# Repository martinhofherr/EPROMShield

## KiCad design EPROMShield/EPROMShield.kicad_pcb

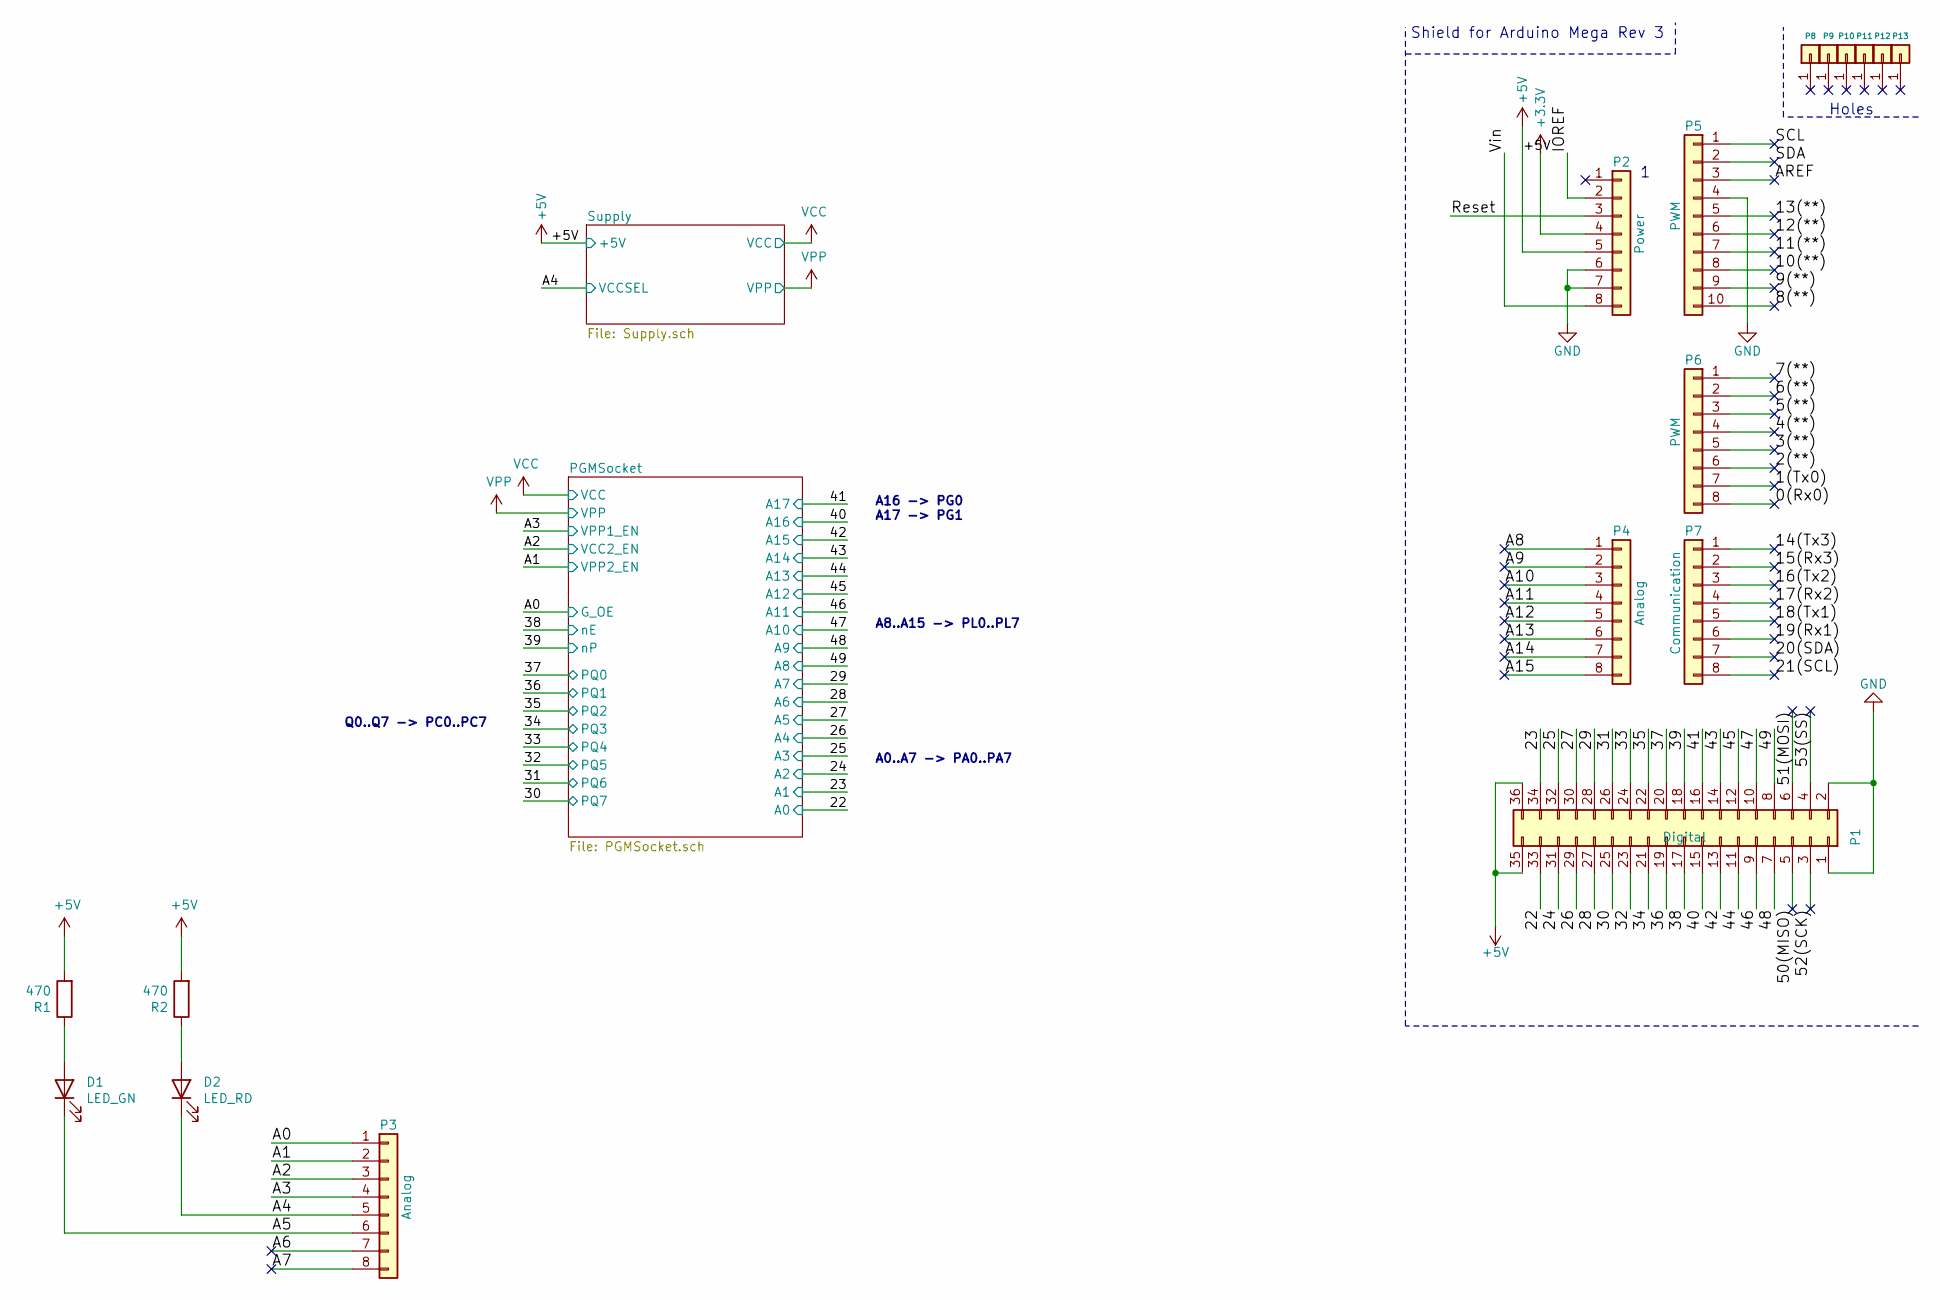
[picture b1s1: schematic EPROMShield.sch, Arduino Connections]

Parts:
D1: LED_GN; LED_1206_3216Metric_Pad1.42x1.75mm_HandSolder
D2: LED_RD; LED_1206_3216Metric_Pad1.42x1.75mm_HandSolder
P1: Digital; Socket_Strip_Arduino_2x18
P2: Power; Socket_Strip_Arduino_1x08
P3, P4: Analog; Socket_Strip_Arduino_1x08
P5: PWM; Socket_Strip_Arduino_1x10
P6: PWM; Socket_Strip_Arduino_1x08
P7: Communication; Socket_Strip_Arduino_1x08
P8, P9, P10, P11, P12, P13: CONN_01X01; Arduino_1pin
R1, R2: 470; R_0805_2012Metric_Pad1.20x1.40mm_HandSolder

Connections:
+3V3: P2.4
+5V: P1.35, P1.36, P2.5, R1.2, R2.2; also elsewhere on the board
/0(Rx0): P6.8
/1(Tx0): P6.7
/2(**): P6.6
/3(**): P6.5
/4(**): P6.4
/5(**): P6.3
/6(**): P6.2
/7(**): P6.1
/8(**): P5.10
/9(**): P5.9
/10(**): P5.8
/11(**): P5.7
/12(**): P5.6
/13(**): P5.5
/14(Tx3): P7.1
/15(Rx3): P7.2
/16(Tx2): P7.3
/17(Rx2): P7.4
/18(Tx1): P7.5
/19(Rx1): P7.6
/20(SDA): P7.7
/21(SCL): P7.8
/22: P1.33; also elsewhere on the board
/23: P1.34; also elsewhere on the board
/24: P1.31; also elsewhere on the board
/25: P1.32; also elsewhere on the board
/26: P1.29; also elsewhere on the board
/27: P1.30; also elsewhere on the board
/28: P1.27; also elsewhere on the board
/29: P1.28; also elsewhere on the board
/30: P1.25; also elsewhere on the board
/31: P1.26; also elsewhere on the board
/32: P1.23; also elsewhere on the board
/33: P1.24; also elsewhere on the board
/34: P1.21; also elsewhere on the board
/35: P1.22; also elsewhere on the board
/36: P1.19; also elsewhere on the board
/37: P1.20; also elsewhere on the board
/38: P1.17; also elsewhere on the board
/39: P1.18; also elsewhere on the board
/40: P1.15; also elsewhere on the board
/41: P1.16; also elsewhere on the board
/42: P1.13; also elsewhere on the board
/43: P1.14; also elsewhere on the board
/44: P1.11; also elsewhere on the board
/45: P1.12; also elsewhere on the board
/46: P1.9; also elsewhere on the board
/47: P1.10; also elsewhere on the board
/48: P1.7; also elsewhere on the board
/49: P1.8; also elsewhere on the board
/50(MISO): P1.5
/51(MOSI): P1.6
/52(SCK): P1.3
/53(SS): P1.4
/A0: P3.1; also elsewhere on the board
/A1: P3.2; also elsewhere on the board
/A2: P3.3; also elsewhere on the board
/A3: P3.4; also elsewhere on the board
/A4: D2.1 (K), P3.5; also elsewhere on the board
/A5: D1.1 (K), P3.6
/A6: P3.7
/A7: P3.8
/A8: P4.1
/A9: P4.2
/A10: P4.3
/A11: P4.4
/A12: P4.5
/A13: P4.6
/A14: P4.7
/A15: P4.8
/AREF: P5.3
/IOREF: P2.2
/Reset: P2.3
/SCL: P5.1
/SDA: P5.2
/Vin: P2.8
GND: P1.1, P1.2, P2.6, P2.7, P5.4; also elsewhere on the board
unnamed: D1.2 (A), R1.1
unnamed: D2.2 (A), R2.1

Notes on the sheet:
Shield for Arduino Mega Rev 3
Holes
Q0..Q7 -> PC0..PC7
A0..A7 -> PA0..PA7
A8..A15 -> PL0..PL7
A16 -> PG0 A17 -> PG1

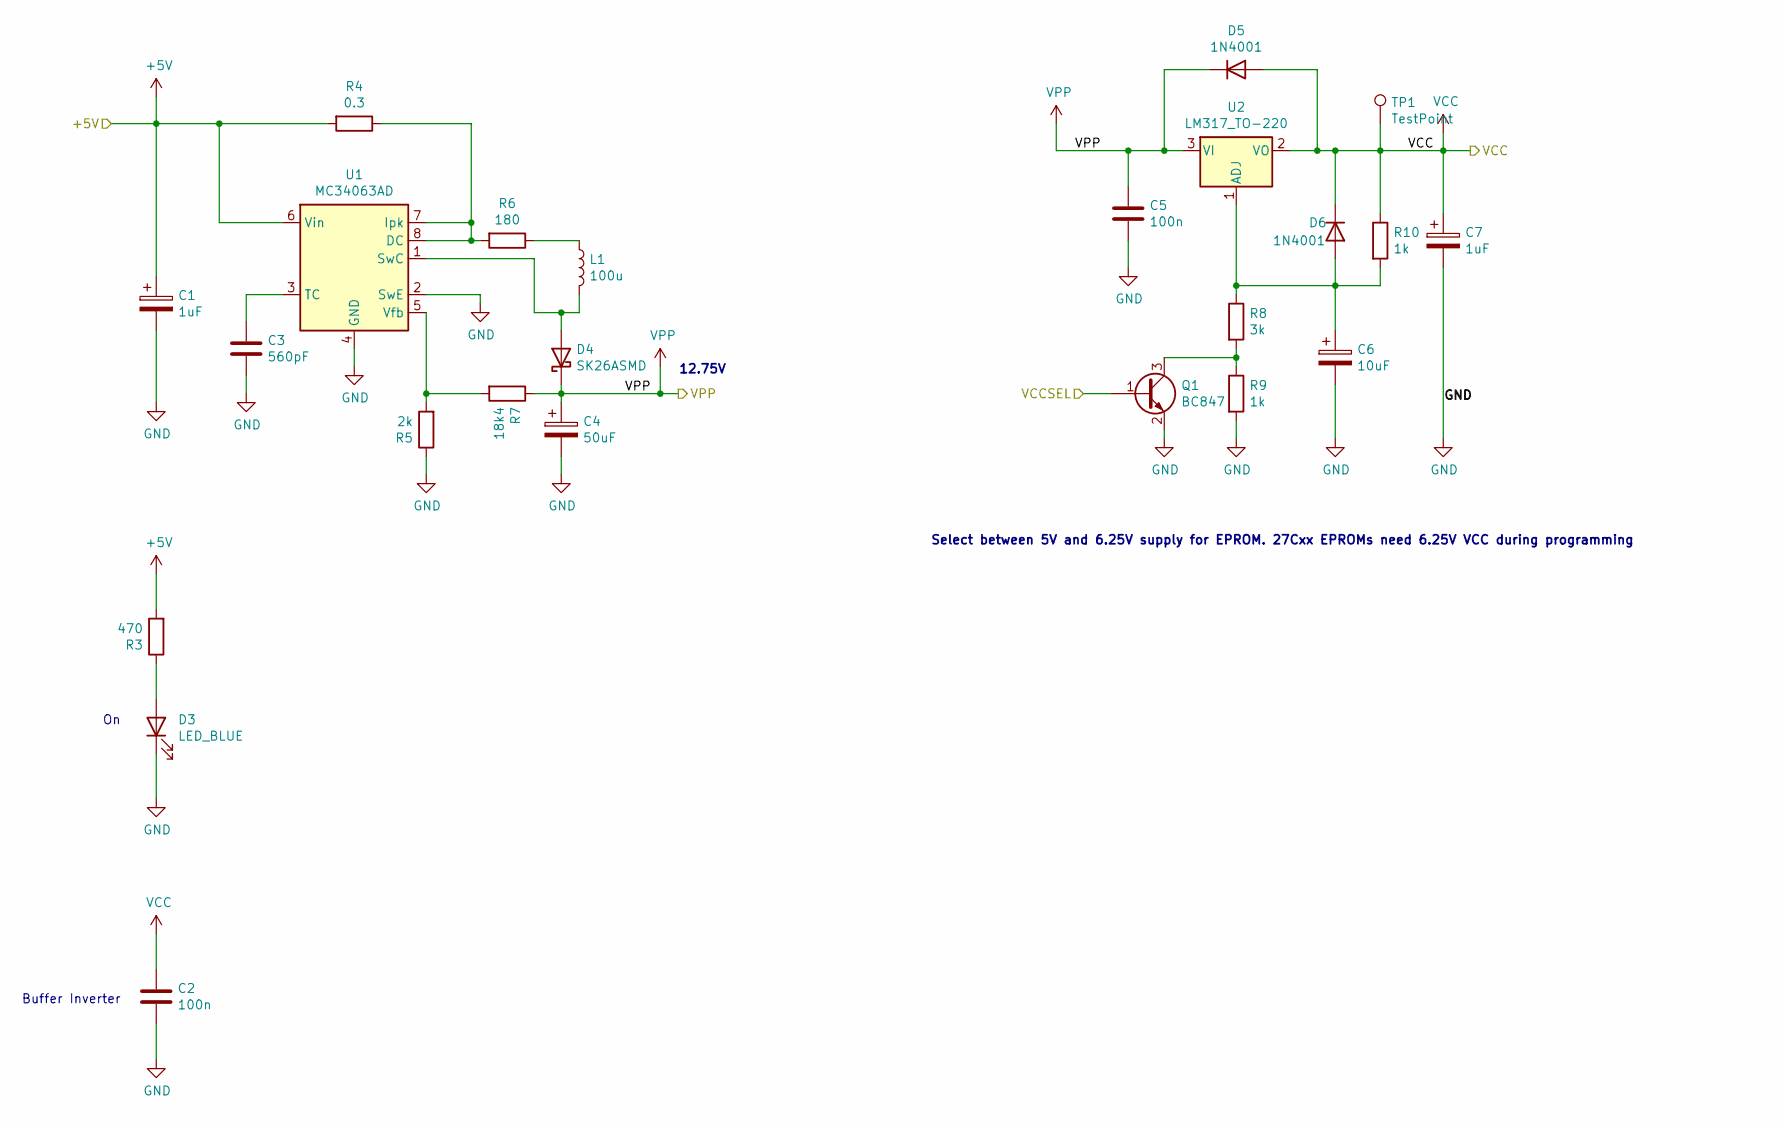
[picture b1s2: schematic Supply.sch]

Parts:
C1: 1uF; CP_Radial_D4.0mm_P1.50mm
C2, C5: 100n; C_0805_2012Metric_Pad1.18x1.45mm_HandSolder
C3: 560pF; C_0805_2012Metric_Pad1.18x1.45mm_HandSolder
C4: 50uF; CP_Radial_D6.3mm_P2.50mm
C6: 10uF; CP_Radial_D6.3mm_P2.50mm
C7: 1uF; CP_Radial_D5.0mm_P2.50mm
D3: LED_BLUE; LED_1206_3216Metric_Pad1.42x1.75mm_HandSolder
D4: SK26ASMD; D_SMA_Handsoldering
D5, D6: 1N4001; D_MELF
L1: 100u; L_Fastron_PISN_Handsoldering
Q1: BC847; SOT-23
R3: 470; R_0805_2012Metric_Pad1.20x1.40mm_HandSolder
R4: 0.3; R_1206_3216Metric_Pad1.30x1.75mm_HandSolder
R5: 2k; R_0805_2012Metric_Pad1.20x1.40mm_HandSolder
R6: 180; R_0805_2012Metric_Pad1.20x1.40mm_HandSolder
R7: 18k4; R_0805_2012Metric_Pad1.20x1.40mm_HandSolder
R8: 3k; R_0805_2012Metric_Pad1.20x1.40mm_HandSolder
R9, R10: 1k; R_0805_2012Metric_Pad1.20x1.40mm_HandSolder
TP1: TestPoint; TestPoint_Pad_D2.0mm
U1: MC34063AD; SOIC-8_3.9x4.9mm_P1.27mm
U2: LM317_TO-220; TO-220F-3_Horizontal_TabDown

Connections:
+5V: C1.1, R3.2, R4.2, U1.6 (Vin); also elsewhere on the board
/A4: Q1.1 (B); also elsewhere on the board
GND: C1.2, C2.2, C3.2, C4.2, C5.2, C6.2, C7.2, D3.1 (K), Q1.2 (E), R5.1, R9.2, U1.2 (SwE), U1.4 (GND); also elsewhere on the board
unnamed: C3.1, U1.3 (TC)
unnamed: C6.1, D6.2 (A), R8.1, R10.2, U2.1 (ADJ)
unnamed: D3.2 (A), R3.1
unnamed: D4.2 (A), L1.2, U1.1 (SwC)
unnamed: L1.1, R6.1
unnamed: Q1.3 (C), R8.2, R9.1
unnamed: R4.1, R6.2, U1.7 (Ipk), U1.8 (DC)
unnamed: R5.2, R7.2, U1.5 (Vfb)
VCC: C2.1, C7.1, D5.2 (A), D6.1 (K), R10.1, TP1.1, U2.2 (VO); also elsewhere on the board
VPP: C4.1, C5.1, D4.1 (K), D5.1 (K), R7.1, U2.3 (VI); also elsewhere on the board

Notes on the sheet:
Buffer Inverter
Select between 5V and 6.25V supply for EPROM. 27Cxx EPROMs need 6.25V VCC during programming
12.75V

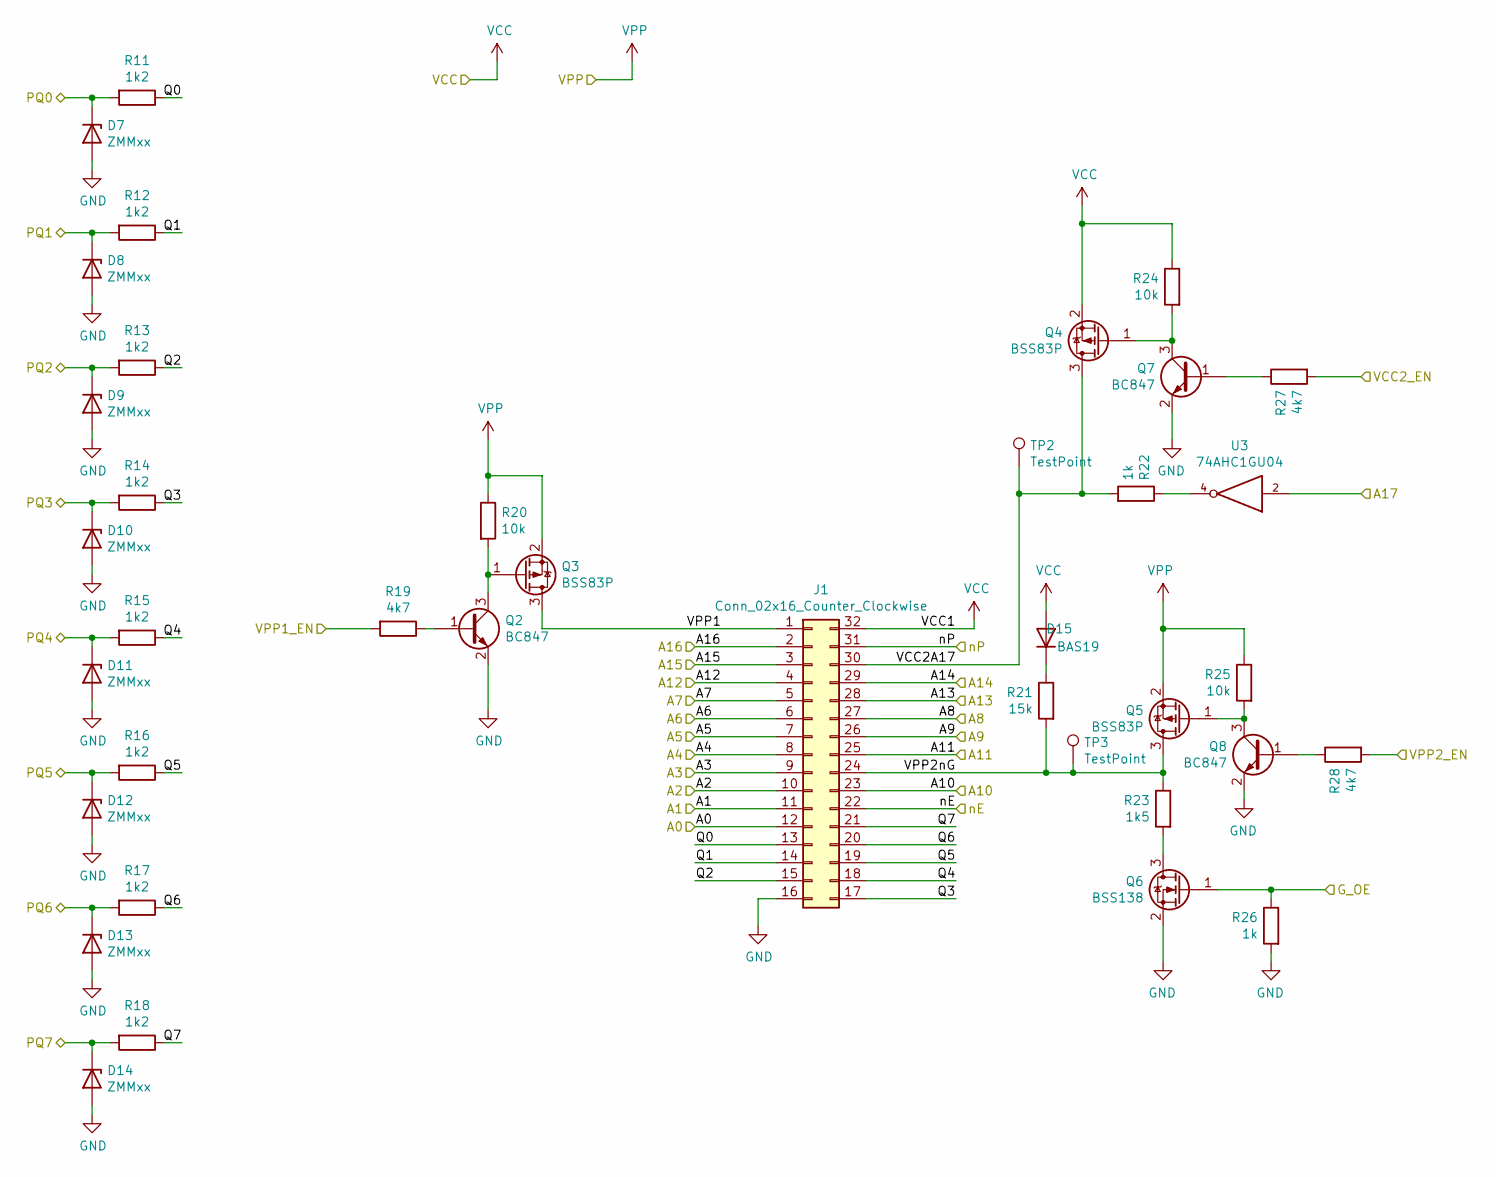
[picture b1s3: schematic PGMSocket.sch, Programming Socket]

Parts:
D7, D8, D9, D10, D11, D12, D13, D14: ZMMxx; D_MiniMELF
D15: BAS19; SOT-23
J1: Conn_02x16_Counter_Clockwise; DIP_Socket-32_W11.9_W12.7_W15.24_W17.78_W18.5_3M_232-1285-0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
Q2, Q7, Q8: BC847; SOT-23
Q3, Q4, Q5: BSS83P; SOT-23
Q6: BSS138; SOT-23
R11, R12, R13, R14, R15, R16, R17, R18: 1k2; R_0805_2012Metric_Pad1.20x1.40mm_HandSolder
R19, R27, R28: 4k7; R_0805_2012Metric_Pad1.20x1.40mm_HandSolder
R20, R24, R25: 10k; R_0805_2012Metric_Pad1.20x1.40mm_HandSolder
R21: 15k; R_0805_2012Metric_Pad1.20x1.40mm_HandSolder
R22, R26: 1k; R_0805_2012Metric_Pad1.20x1.40mm_HandSolder
R23: 1k5; R_0805_2012Metric_Pad1.20x1.40mm_HandSolder
TP2, TP3: TestPoint; TestPoint_Pad_D2.0mm
U3: 74AHC1GU04; SOT-353_SC-70-5_Handsoldering

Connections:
/22: J1.12; also elsewhere on the board
/23: J1.11; also elsewhere on the board
/24: J1.10; also elsewhere on the board
/25: J1.9; also elsewhere on the board
/26: J1.8; also elsewhere on the board
/27: J1.7; also elsewhere on the board
/28: J1.6; also elsewhere on the board
/29: J1.5; also elsewhere on the board
/30: D14.1 (K), R18.2; also elsewhere on the board
/31: D13.1 (K), R17.2; also elsewhere on the board
/32: D12.1 (K), R16.2; also elsewhere on the board
/33: D11.1 (K), R15.2; also elsewhere on the board
/34: D10.1 (K), R14.2; also elsewhere on the board
/35: D9.1 (K), R13.2; also elsewhere on the board
/36: D8.1 (K), R12.2; also elsewhere on the board
/37: D7.1 (K), R11.2; also elsewhere on the board
/38: J1.22; also elsewhere on the board
/39: J1.31; also elsewhere on the board
/40: J1.2; also elsewhere on the board
/41: U3.2; also elsewhere on the board
/42: J1.3; also elsewhere on the board
/43: J1.29; also elsewhere on the board
/44: J1.28; also elsewhere on the board
/45: J1.4; also elsewhere on the board
/46: J1.25; also elsewhere on the board
/47: J1.23; also elsewhere on the board
/48: J1.26; also elsewhere on the board
/49: J1.27; also elsewhere on the board
/A0: Q6.1 (G), R26.1; also elsewhere on the board
/A1: R28.2; also elsewhere on the board
/A2: R27.2; also elsewhere on the board
/A3: R19.2; also elsewhere on the board
/PGMSocket/Q0: J1.13, R11.1
/PGMSocket/Q1: J1.14, R12.1
/PGMSocket/Q2: J1.15, R13.1
/PGMSocket/Q3: J1.17, R14.1
/PGMSocket/Q4: J1.18, R15.1
/PGMSocket/Q5: J1.19, R16.1
/PGMSocket/Q6: J1.20, R17.1
/PGMSocket/Q7: J1.21, R18.1
/PGMSocket/VCC2A17: J1.30, Q4.3 (D), R22.2, TP2.1
/PGMSocket/VPP1: J1.1, Q3.3 (D)
/PGMSocket/VPP2nG: J1.24, Q5.3 (D), R21.2, R23.1, TP3.1
GND: D7.2 (A), D8.2 (A), D9.2 (A), D10.2 (A), D11.2 (A), D12.2 (A), D13.2 (A), D14.2 (A), J1.16, Q2.2 (E), Q6.2 (S), Q7.2 (E), Q8.2 (E), R26.2, U3.3 (GND); also elsewhere on the board
unnamed: D15.3 (K), R21.1
unnamed: Q2.1 (B), R19.1
unnamed: Q2.3 (C), Q3.1 (G), R20.2
unnamed: Q4.1 (G), Q7.3 (C), R24.2
unnamed: Q5.1 (G), Q8.3 (C), R25.2
unnamed: Q6.3 (D), R23.2
unnamed: Q7.1 (B), R27.1
unnamed: Q8.1 (B), R28.1
unnamed: R22.1, U3.4
VCC: D15.1 (A), J1.32, Q4.2 (S), R24.1, U3.5 (VCC); also elsewhere on the board
VPP: Q3.2 (S), Q5.2 (S), R20.1, R25.1; also elsewhere on the board

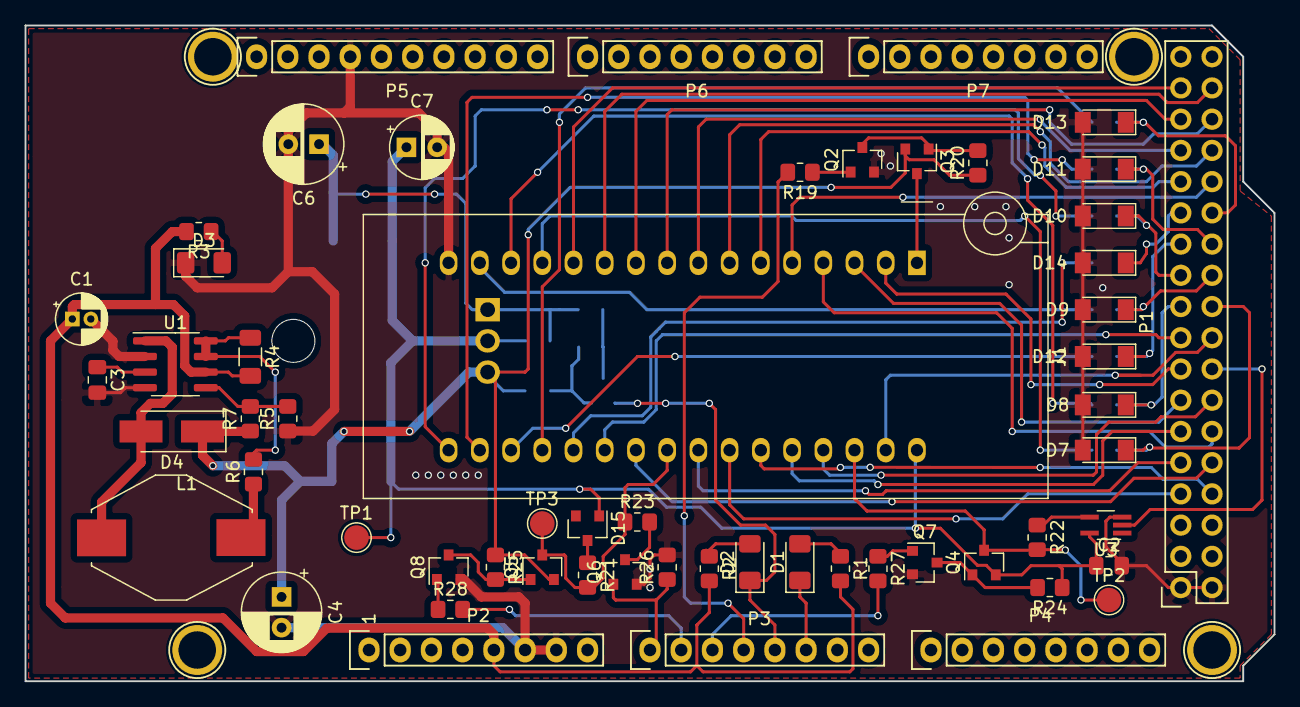
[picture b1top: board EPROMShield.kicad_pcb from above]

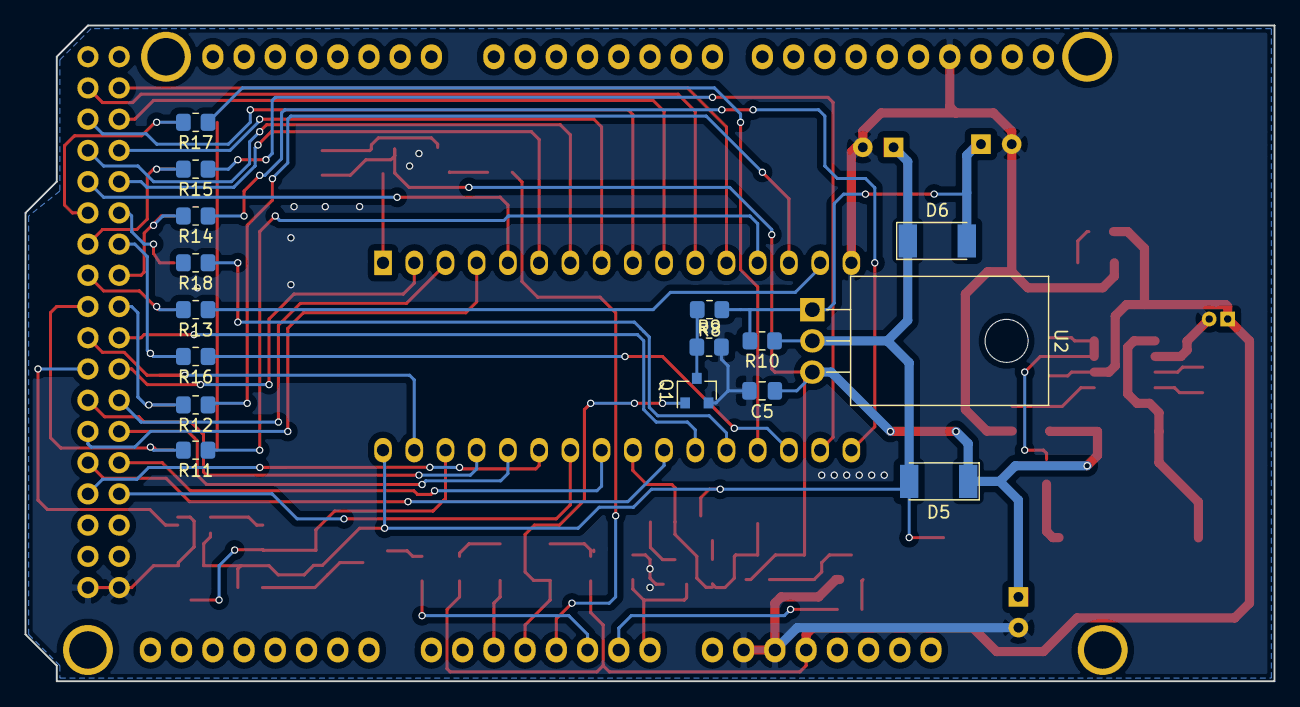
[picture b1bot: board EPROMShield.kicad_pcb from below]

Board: 2 copper layers, 101.6 x 53.3 mm, 77 parts (16 on the bottom side), 68 nets.

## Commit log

2021-08-22 Finished schematic added caluclation for boost converter
2021-08-22 Footprints associated
2021-08-22 Added netlist, fixed footprint L1
2021-08-22 First shot at component placement. Fixed VCC connection for Inverter
2021-08-24 First Version routing is done
2021-08-24 Routing update
2021-08-27 Added EPROM Overview
